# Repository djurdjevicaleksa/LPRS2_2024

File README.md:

# AC-Logger - LPRS2_2024 Projekat

## Opis
U ovom projektu implementirali smo sistem za belezenje podataka o naizmenicnoj struji (AC) pomocu Arduina i dodatnog shield-a na kom smo prikacili RTC modul i modul za SD karticu. Sistem omogucava merenje vrednosti analognog signala, njihovo vremensko oznacavanje i skladistenje na SD karticu. Na ovaj nacin smo pruzili pouzdan i precizan nacin za pracenje karakteristika naizmenicne struje, sto moze biti korisno u razlicitim aplikacijama kao sto su energetski nadzor, optimizacija potrosnje elektricne energije i analiza kvaliteta struje.

## Struktura
* U okviru `SineReadingTest` direktorijuma postoje sve potrebne biblioteke
* Takodje, nalazi se i glavni `SineReadingTest.ino` fajl

## Setup
* Otvori se `SineReadingTest.ino` u *ArduinoIDE* i uploaduje se na Arduino koji je povezan na racunar
* Nakon sto je odradjen upload, ocitavanje vrednosti i upis na SD karticu se odvija automatski
* Na *Serial Monitoru* je moguce debagovati greske i pratiti vrednosti koje se upisuju na SD karticu

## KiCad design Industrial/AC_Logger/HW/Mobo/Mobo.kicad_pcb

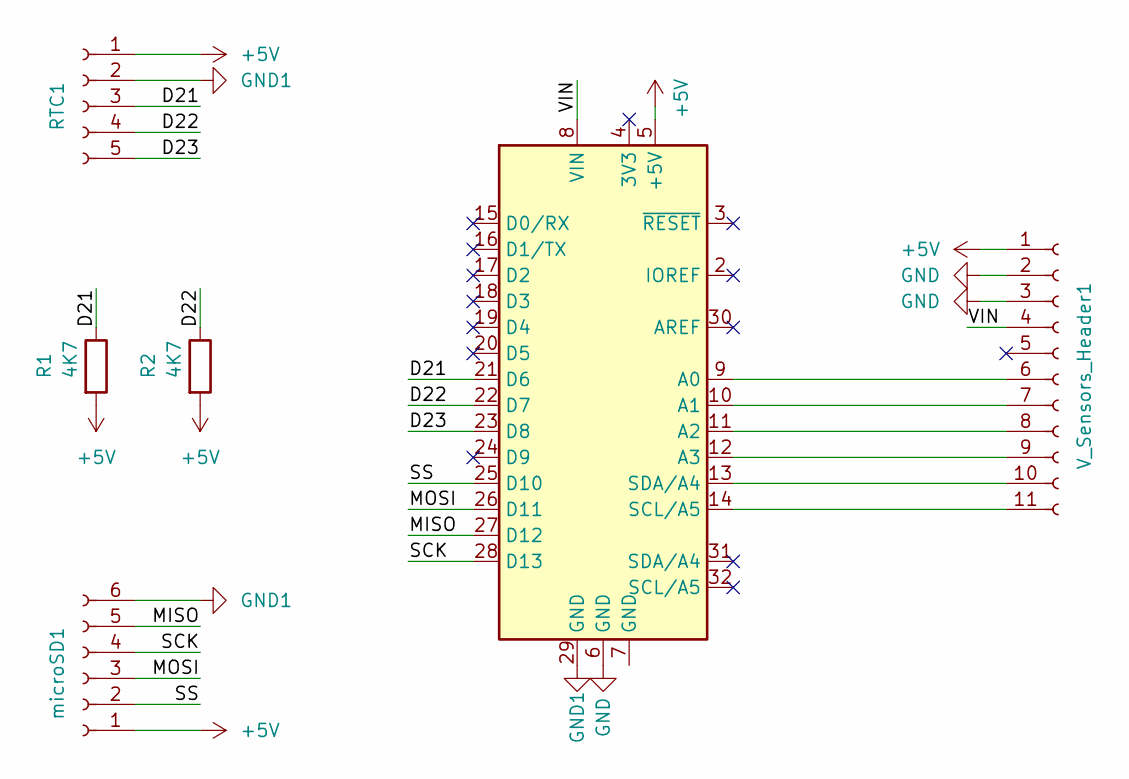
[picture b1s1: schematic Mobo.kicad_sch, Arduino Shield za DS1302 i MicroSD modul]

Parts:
Arduino1: Arduino UNO R3; Arduino_UNO_R3_WithMountingHoles_Snapped_to_P2.54mm
R1, R2: 4K7; R_Axial_DIN0207_L6.3mm_D2.5mm_P7.62mm_Horizontal
RTC1: Conn_01x05_Female; PinSocket_1x05_P2.54mm_Vertical
V_Sensors_Header1: Conn_01x11_Female; PinSocket_1x11_P2.54mm_Vertical
microSD1: Conn_01x06_Female; PinSocket_1x06_P2.54mm_Vertical

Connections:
+5V: Arduino1.5 (+5V), R1.2, R2.2, RTC1.1, V_Sensors_Header1.1, microSD1.1
/D21: Arduino1.21 (D6), R1.1, RTC1.3
/D22: Arduino1.22 (D7), R2.1, RTC1.4
/D23: Arduino1.23 (D8), RTC1.5
/MISO: Arduino1.27 (D12), microSD1.5
/MOSI: Arduino1.26 (D11), microSD1.3
/SCK: Arduino1.28 (D13), microSD1.4
/SS: Arduino1.25 (D10), microSD1.2
/VIN: Arduino1.8 (VIN), V_Sensors_Header1.4
GND: Arduino1.6 (GND), V_Sensors_Header1.2, V_Sensors_Header1.3
GND1: Arduino1.29 (GND), RTC1.2, microSD1.6
unnamed: Arduino1.9 (A0), V_Sensors_Header1.6
unnamed: Arduino1.10 (A1), V_Sensors_Header1.7
unnamed: Arduino1.11 (A2), V_Sensors_Header1.8
unnamed: Arduino1.12 (A3), V_Sensors_Header1.9
unnamed: Arduino1.13 (SDA/A4), V_Sensors_Header1.10
unnamed: Arduino1.14 (SCL/A5), V_Sensors_Header1.11

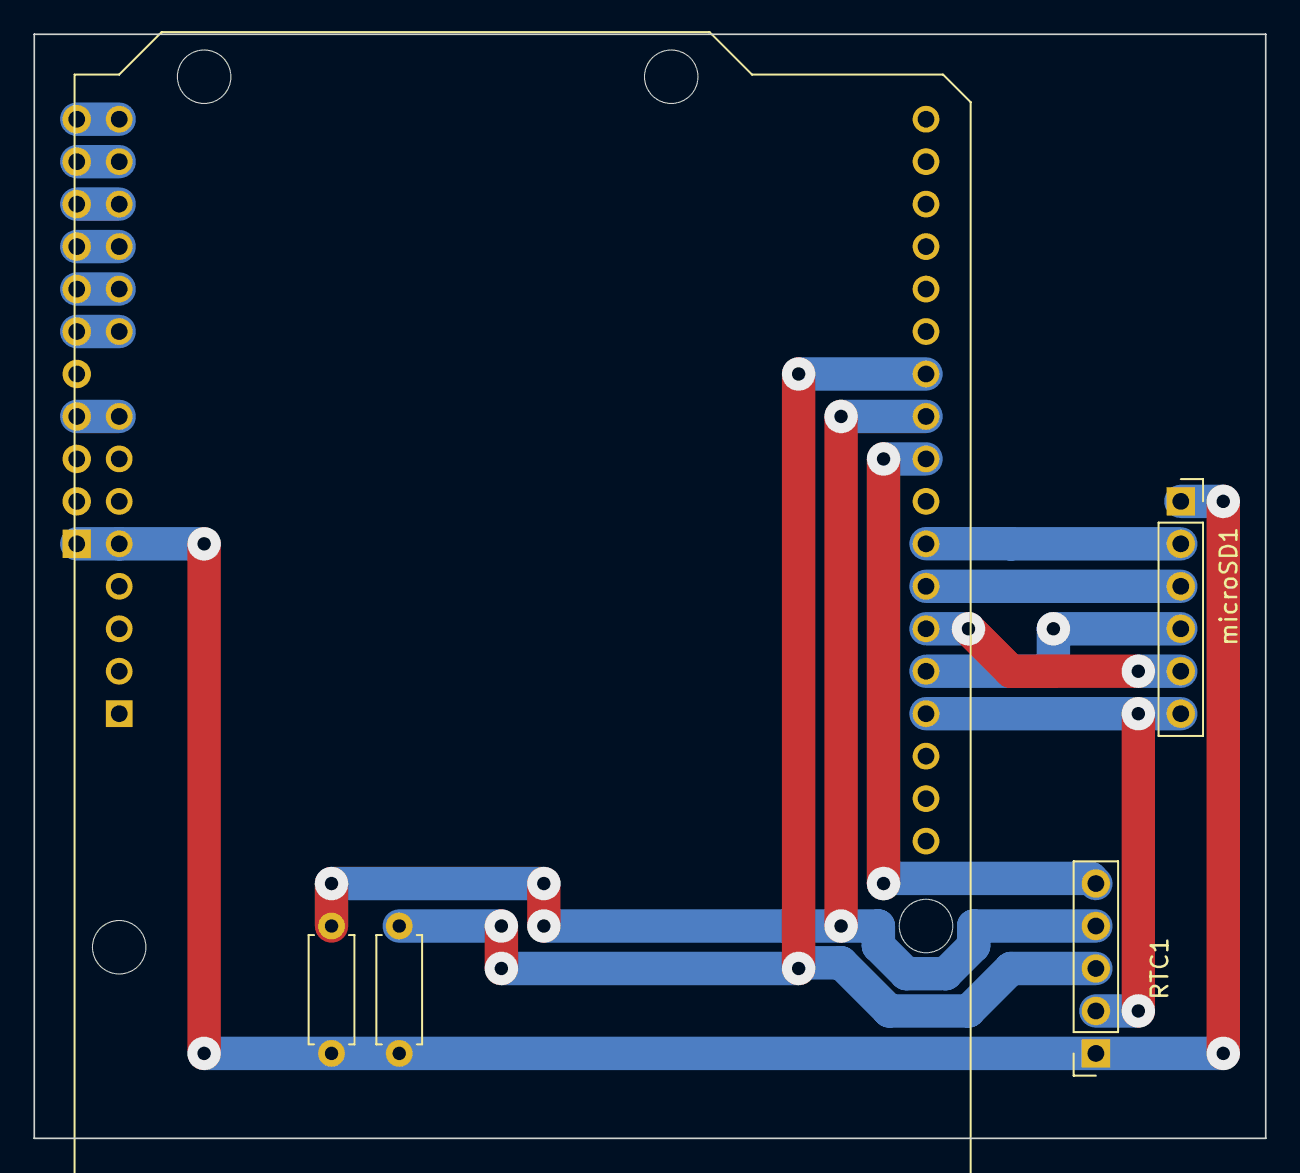
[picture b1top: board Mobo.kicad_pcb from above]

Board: 2 copper layers, 73.7 x 66.0 mm, 6 parts (1 on the bottom side), 17 nets.

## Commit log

2024-05-30 Removing what not needed.
2024-05-30 Initial sch of mobo. Wrong PCB.
2024-05-30 Not needed.
2024-05-30 Libs
2024-05-30 Started new PCB
2024-06-04 Finished stripboard design
2024-06-06 Last last edit to pcb
2024-06-17 PCB final, instructions for handling SD module
2024-06-18 Finising touches on PCB and Schematic
2024-06-19 pre razvaljivanja adc-a
2024-06-19 Fixed errors in bit fields, should read well now
2024-06-20 20.6.
2024-06-20 Testiranje i izlaz za python graf
2024-06-21 v1.0
